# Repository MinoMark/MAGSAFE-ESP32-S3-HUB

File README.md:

# MAGSAFE ESP32-S3 HUB
**Don't get up, just use this...**

(Read bottom before reading BOM)

## About My Project

What is my project? My project is one of a kind! I am using an ESP32-S3 microcontroller chip to power a smart 2.8" TFT touchscreen. As mentioned in the title, it is listed as being MagSafe compatible, which is ingenious, right? Who does not want to have it charging 24/7? Or maybe not? Well, that has been solved too! I have added a 3.7V 5000mAh LiPo battery that can last well over 24 hours. But that is not all! I have also included an audio amplifier with a super loud and crisp speaker so you can hear those alerts and alarms from meters away.

I’ve made this project because I am tired of opening my laptop just to have a look at the time, set a timer, turn on smart lights, or do almost anything else. With my design, I’ll be able to control these all in one. You can have it play soothing music or play annoying alarms whenever.

**How to use:**

Plug it into the dedicated USB-C port at the bottom side with a USB-C cable or any compatible iPhone MagSafe charger. Let it charge for 10 minutes to an hour to fully charge. For MagSafe, let it charge for 30 minutes to an hour and 15 minutes.

## Schematics
The schematics of my final design, what I'll be using to make the main PCB.

## PCB
The fully routed PCB, with fun easter egg and smart eletrical wiring choices that save money and change the path of electricity more efficiently.

## CAD
A full design of the parts (except some models impossible to source)
.png>) 
.png>) 
.png>)

## BOM

| Part | Type | Quantity | Unit price (AUD) | Line total (AUD) | Link | Vendor | Funding | Notes | Index | LCSC# | MPN | Package | RoHS | MOQ | Multiple |
|---|---|---:|---:|---:|---|---|---|---|---:|---|---|---|---|---:|---:|
| 0Ω ±1% 62.5mW 0402 Thick Film Resistor | Part | 4 | 0.0011 | 0.0044 | https://www.lcsc.com/product-detail/C17168.html | UNI-ROYAL | Grant | This is min you can buy | 1 | C17168 | 0402WGF0000TCE | 0402 | yes | 100 | 100 |
| Crystal 32.768kHz ±20ppm 6pF 55kΩ SMD3215-2P | Part | 2 | 0.6046 | 0.60 | https://www.lcsc.com/product-detail/C1985240.html | ABRACON | Grant | This is min you can buy | 2 | C1985240 | ABS07-120-32.768KHZ-T | SMD3215-2P | yes | 1 | 1 |
| 3.3V Positive Fixed SOT-89-5 Voltage Regulators - Linear, Low Drop Out (LDO) Regulators RoHS | Part | 2 | 0.5913 | 0.59 | https://www.lcsc.com/product-detail/C460397.html | DIODES | Grant | This is min you can buy | 3 | C460397 | AP7361C-33Y5-13 | SOT-89-5 | yes | 1 | 1 |
| 14VC Clamp 5.5A Ipp ESD DIODE SOT-666-6 | Part | 2 | 0.1571 | 0.79 | https://www.lcsc.com/product-detail/C2827693.html | TECH PUBLIC | Grant | This is min you can buy | 4 | C2827693 | USBLC6-2P6 | SOT-666-6 | yes | 5 | 5 |
| Tactile Switch SPST 250gf 2.5mm Gull Wing 6.1mm x 3.7mm Surface Mount | Part | 4 | 0.0415 | 0.42 | https://www.lcsc.com/product-detail/C255802.html | HYP | Grant | This is min you can buy | 5 | C255802 | 1TS002E-2500-2501-CT | SMD,6x3.7mm | yes | 10 | 10 |
| 22Ω ±1% 62.5mW 0402 Thick Film Resistor | Part | 4 | 0.0019 | 0.0076 | https://www.lcsc.com/product-detail/C25092.html | UNI-ROYAL | Grant | This is min you can buy | 6 | C25092 | 0402WGF220JTCE | 0402 | yes | 100 | 100 |
| 5.1kΩ ±1% 62.5mW 0402 Thick Film Resistor | Part | 4 | 0.0023 | 0.0092 | https://www.lcsc.com/product-detail/C25905.html | UNI-ROYAL | Grant | This is min you can buy | 7 | C25905 | 0402WGF5101TCE | 0402 | yes | 100 | 100 |
| 100nF ±10% 50V Ceramic Capacitor X7R 0402 | Part | 2 | 0.009 | 0.018 | https://www.lcsc.com/product-detail/C307331.html | Samsung Electro-Mechanics | Grant | This is min you can buy | 8 | C307331 | CL05B104KB54PNC | 0402 | yes | 100 | 100 |
| Pre-Biased Bipolar Transistor (BJT) 50V 100mA 150mW Surface Mount SOT-363 | Part | 2 | 0.0502 | 0.50 | https://www.lcsc.com/product-detail/C62892.html | JSCJ | Grant | This is min you can buy | 9 | C62892 | UMH3N | SOT-363 | yes | 10 | 10 |
| 22Ω ±5% 62.5mW 0402 Thick Film Resistor | Part | 4 | 0.0017 | 0.0068 | https://www.lcsc.com/product-detail/C25152.html | UNI-ROYAL | Grant | This is min you can buy | 10 | C25152 | 0402WGJ0220TCE | 0402 | yes | 100 | 100 |
| DIODES AP2112K-3.3TRG1 | Part | 4 | 0.1848 | 0.7392 | https://www.lcsc.com/product-detail/C51118.html?s_z=n_q_c51118&globalKeyword=c51118 | DIODES | Grant | This is min you can buy | 11 | C51118 | AP2112K-3.3TRG1 | SOT-25-5 | yes | 5 | 5 |
| 2.4GHz ESP32-S3R8 -103.5dBm SMD,19.2x18mm RF Transceiver Modules and Modems RoHS | Part | 2 | 5.2355 | 5.24 | https://www.lcsc.com/product-detail/C3013946.html | ESPRESSIF | Grant | This is min you can buy | 12 | C3013946 | ESP32-S3-WROOM-1U-N16R8 | SMD,19.2x18mm | yes | 1 | 1 |
| USB-C (USB TYPE-C) Receptacle Connector 16 Position Surface Mount | Part | 2 | 0.1736 | 0.87 | https://www.lcsc.com/product-detail/C165948.html | Korean Hroparts Elec | Grant | This is min you can buy | 13 | C165948 | TYPE-C-31-M-12 | SMD | yes | 5 | 5 |
| 14.1VC Clamp 11.2A Ipp TVS DIODE SOD-523 | Part | 2 | 0.0487 | 0.49 | https://www.lcsc.com/product-detail/C61148.html | onsemi | Grant | This is min you can buy | 14 | C61148 | ESD5Z3.3T1G | SOD-523 | yes | 10 | 10 |
| Red 625nm LED Indication - Discrete 2.3V 0603 | Part | 2 | 0.0036 | 0.0072 | https://www.lcsc.com/product-detail/C965799.html | XINGLIGHT | Grant | This is min you can buy | 15 | C965799 | XL-1608SURC-06 | 0603 | yes | 100 | 100 |
| Diode Independent 40V 3A Surface Mount SMA(DO-214AC) | Part | 6 | 0.0337 | 0.67 | https://www.lcsc.com/product-detail/C8678.html | MDD(Microdiode Semiconductor) | Grant | This is min you can buy | 16 | C8678 | SS34 | SMA(DO-214AC) | yes | 20 | 20 |
| 22uF ±20% 25V Ceramic Capacitor X5R 0805 | Part | 2 | 0.1852 | 3.70 | https://www.lcsc.com/product-detail/C45783.html | Samsung Electro-Mechanics | Grant | This is min you can buy | 17 | C45783 | CL21A226MAQNNNE | 0805 | yes | 20 | 20 |
| 10uF ±20% 10V Ceramic Capacitor X5R 0402 | Part | 10 | 0.0304 | 1.82 | https://www.lcsc.com/product-detail/C315248.html | Samsung Electro-Mechanics | Grant | This is min you can buy | 18 | C315248 | CL05A106MP5NUNC | 0402 | yes | 20 | 20 |
| 1uF ±10% 25V Ceramic Capacitor X5R 0402 | Part | 2 | 0.0059 | 0.0118 | https://www.lcsc.com/product-detail/C52923.html | Samsung Electro-Mechanics | Grant | This is min you can buy | 19 | C52923 | CL05A105KA5NQNC | 0402 | yes | 100 | 100 |
| MAX98357A audio amplifier | Part | 1 | 3.01 | 3.01 | https://www.aliexpress.com/item/1005007003802663.html?spm=a2g0o.productlist.main.4.2bd23ce0doG6x8&aem_p4p_detail=202611050133081315319932123740002772996&algo_pvid=0ad6be40-46e3-4f00-9430-e9820924795f&algo_exp_id=0ad6be40-46e3-4f00-9430-e9820924795f-3&pdp_ext_f=%7B%22order%22%3A%223834%22%2C%22spu_best_type%22%3A%22price%22%2C%22eval%22%3A%221%22%2C%22fromPage%22%3A%22search%22%7D&pdp_npi=6%40dis%21AUD%212.99%212.84%21%21%2113.80%2113.11%21%402101ca9517938711880116699e0d41%2112000052658790894%21sea%21AU%212961347876%21X%211%210%21n_tag%3A-29919%3Bd%3A20f6a0d2%3Bm03_new_user%3A-29895%3BpisId%3A5000000220905999&curPageLogUid=gHNWoxg3Cup0&utparam-url=scene%3Asearch%7Cquery_from%3A%7Cx_object_id%3A1005007003802663%7C_p_origin_prod%3A&search_p4p_id=202611050133081315319932123740002772996_1 | AliExpress | Grant | | 20 | N/A | N/A | 1PCS | yes | 1 | 1 |
| Wireless charger receiver | Part | 1 | 4.26 | 4.26 | https://www.aliexpress.com/item/1005006917890401.html?spm=a2g0o.productlist.main.21.5befc5e30wHdxF&algo_pvid=c3f727d4-7764-4de2-9cfe-4073aea75173&algo_exp_id=c3f727d4-7764-4de2-9cfe-4073aea75173-18&pdp_ext_f=%7B%22order%22%3A%22260%22%2C%22spu_best_type%22%3A%22price%22%2C%22eval%22%3A%22price%22%2C%22fromPage%22%3A%22search%22%7D&pdp_npi=6%40dis%21AUD%213.98%213.49%21%21%212.75%212.41%21%402101d2e717938715347906588e0f1b%2112000038722150536%21sea%21AU%212961347876%21X%211%210%21n_tag%3A-29919%3Bd%3A20f6a0d2%3Bm03_new_user%3A-29895%3BpisId%3A5000000220770329&curPageLogUid=ptJgFovmIGzU&utparam-url=scene%3Asearch%7Cquery_from%3A%7Cx_object_id%3A1005006917890401%7C_p_origin_prod%3A | AliExpress | Grant | | 21 | N/A | N/A | 5W | yes | 1 | 1 |
| Battery management board | Part | 1 | 1.06 | 1.06 | https://www.aliexpress.com/item/1005013472412754.html?spm=a2g0o.productlist.main.9.7fb4e999hY7Rre&algo_pvid=98fe2f10-0cd6-416a-bbd2-9b577de21ebe&algo_exp_id=98fe2f10-0cd6-416a-bbd2-9b577de21ebe-8&pdp_ext_f=%7B%22order%22%3A%225%22%2C%22spu_best_type%22%3A%22price%22%2C%22eval%22%3A%221%22%2C%22fromPage%22%3A%22search%22%7D&pdp_npi=6%40dis%21AUD%212.45%210.97%21%21%2111.31%214.51%21%402101d33417938729376868658e0dc7%2112000061234386246%21sea%21AU%212961347876%21X%211%210%21n_tag%3A-29919%3Bd%3A20f6a0d2%3Bm03_new_user%3A-29895%3BpisId%3A5000000220868114&curPageLogUid=SZ1nXcZwQJOj&utparam-url=scene%3Asearch%7Cquery_from%3A%7Cx_object_id%3A1005013472412754%7C_p_origin_prod%3A | AliExpress | Grant | | 22 | N/A | N/A | 1X-Type C | yes | 1 | 1 |
| 955565 3.7V 5000mAh Polymer Lithium Battery | Part | 1 | 12.47 | 12.47 | https://www.aliexpress.com/item/1005013156740117.html?spm=a2g0o.productlist.main.2.398348ee8Gn6zi&algo_pvid=f6f2868e-1781-4497-a01c-ee345d06bc3b&algo_exp_id=f6f2868e-1781-4497-a01c-ee345d06bc3b-1&pdp_ext_f=%7B%22order%22%3A%222%22%2C%22spu_best_type%22%3A%22price%22%2C%22eval%22%3A%22price%22%2C%22fromPage%22%3A%22search%22%7D&pdp_npi=6%40dis%21AUD%2120.14%2112.69%21%21%2192.85%2158.50%21%4021030f8317938734351546746e0d36%2112000060361345573%21sea%21AU%212961347876%21X%211%210%21n_tag%3A-29919%3Bd%3A20f6a0d2%3Bm03_new_user%3A-29895 | AliExpress | Grant | | 23 | N/A | N/A | 955565 1PCS | yes | 1 | 1 |
| Speaker | Part | 1 | 2.54 | 2.54 | https://www.aliexpress.com/item/1005007640238935.html?spm=a2g0o.detail.pcDetailTopMoreOtherSeller.4.6cacshuCshuCnA&gps-id=pcDetailTopMoreOtherSeller&scm=1007.40050.354490.0&scm_id=1007.40050.354490.0&scm-url=1007.40050.354490.0&pvid=b61e8163-83fe-4c95-9dc5-7b9f26661546&_t=gps-id%3ApcDetailTopMoreOtherSeller%2Cscm-url%3A1007.40050.354490.0%2Cpvid%3Ab61e8163-83fe-4c95-9dc5-7b9f26661546%2Ctpp_buckets%3A668%232846%238110%231995&pdp_ext_f=%7B%22order%22%3A%222631%22%2C%22eval%22%3A%221%22%2C%22sceneId%22%3A%2230050%22%2C%22fromPage%22%3A%22recommend%22%7D&pdp_npi=6%40dis%21AUD%214.06%213.69%21%21%2118.49%2116.82%21%402103117b17940474651706506e0d0b%2112000041608234950%21rec%21AU%212961347876%21XZ%211%210%21n_tag%3A-29919%3Bd%3A20f6a0d2%3Bm03_new_user%3A-29895%3BpisId%3A5000000220905999&utparam-url=scene%3ApcDetailTopMoreOtherSeller%7Cquery_from%3A%7Cx_object_id%3A1005007640238935%7C_p_origin_prod%3A | AliExpress | Grant | | 24 | N/A | N/A | 2535 4 ohm 3W | yes | 1 | 1 |
| 2.8" Touch LCD Screen | Part | 1 | 7.67 | 7.67 | https://www.aliexpress.com/item/1005008556130457.html?spm=a2g0o.detail.pcDetailTopMoreOtherSeller.12.6cacshuCshuCnA&gps-id=pcDetailTopMoreOtherSeller&scm=1007.40050.354490.0&scm_id=1007.40050.354490.0&scm-url=1007.40050.354490.0&pvid=b61e8163-83fe-4c95-9dc5-7b9f26661546&_t=gps-id%3ApcDetailTopMoreOtherSeller%2Cscm-url%3A1007.40050.354490.0%2Cpvid%3Ab61e8163-83fe-4c95-9dc5-7b9f26661546%2Ctpp_buckets%3A668%232846%238110%231995&pdp_ext_f=%7B%22order%22%3A%222115%22%2C%22spu_best_type%22%3A%22price%22%2C%22eval%22%3A%221%22%2C%22sceneId%22%3A%2230050%22%2C%22fromPage%22%3A%22recommend%22%7D&pdp_npi=6%40dis%21AUD%2135.60%2131.55%21%21%21162.02%21143.60%21%402103117b17940474651706506e0d0b%2112000045695652679%21rec%21AU%212961347876%21XZ%211%210%21n_tag%3A-29919%3Bd%3A20f6a0d2%3Bm03_new_user%3A-29895%3BpisId%3A5000000221234826&utparam-url=scene%3ApcDetailTopMoreOtherSeller%7Cquery_from%3A%7Cx_object_id%3A1005008556130457%7C_p_origin_prod%3A | AliExpress | Already own | | 25 | N/A | N/A | 2.8 Inch LCD | yes | 1 | 1 |
| AliExpress Shipping (Australia) | Shipping | 1 | 3.02 | 3.02 | https://www.aliexpress.com/?src=google&albch=fbrnd&acnt=347-178-5672&isdl=y&aff_short_key=UneMJZVf&albcp=22321354204&albag=178985906351&slnk=&trgt=kwd-14802285088&plac=&crea=737351379802&netw=g&device=c&mtctp=e&memo1=&albbt=Google_7_fbrnd&aff_platform=google&albagn=888888&isSmbActive=false&isSmbAutoCall=false&needSmbHouyi=false&gad_source=1&gad_campaignid=22321354204&gbraid=0AAAAAD1qHibUcQdrYeOuuBWuvApxTQOP2&gclid=CjwKCAiAtbvXBhB_EiwAjwv9Jjyvq29gqiMRapaex5iaRvapHnvC2KuxCO2ai3P2B7r6hRykpAxdUhoCgLwQAvD_BwE | AliExpress | Grant | | 26 | N/A | N/A | N/A | N/A | N/A | N/A |
| AliExpress tax | Tax or fee | 1 | 2.52 | 2.52 | https://www.aliexpress.com/?src=google&albch=fbrnd&acnt=347-178-5672&isdl=y&aff_short_key=UneMJZVf&albcp=22321354204&albag=178985906351&slnk=&trgt=kwd-14802285088&plac=&crea=737351379802&netw=g&device=c&mtctp=e&memo1=&albbt=Google_7_fbrnd&aff_platform=google&albagn=888888&isSmbActive=false&isSmbAutoCall=false&needSmbHouyi=false&gad_source=1&gad_campaignid=22321354204&gbraid=0AAAAAD1qHibUcQdrYeOuuBWuvApxTQOP2&gclid=CjwKCAiAtbvXBhB_EiwAjwv9Jjyvq29gqiMRapaex5iaRvapHnvC2KuxCO2ai3P2B7r6hRykpAxdUhoCgLwQAvD_BwE | AliExpress | Grant | | 27 | N/A | N/A | N/A | N/A | N/A | N/A |
| PCBA & PCBA | PCB | 1 | 149.00 | 149.00 | https://jlcpcb.com/?from=VGS&utm_source=google&utm_medium=cpc&utm_campaign=14177189905&gad_source=1&gad_campaignid=14177189905&gbraid=0AAAAABS1Qql1GOgRJWfW55GGh4BVLQ-kr&gclid=CjwKCAiA2MDXBhBUEiwAD-YB-_knJwTwOTv6-qw0cwhvcRU1fMAk8eRsxDyDG89k4pFLfxfHsxuqEBoCV9sQAvD_BwE | JLCONE | Grant | It says in the photo its $150 AUD, but im buying from us so its ok. | 28 | N/A | N/A | N/A | no | N/A | N/A |
| **Total** | | | | **202.0442** | | | | | | | | | | | |
| **Grant total** | | | | **194.3742** | | | | | | | | | | | |

# IMPORTANT READ BELOW

**Just to let you know:**

The total for the PCB is $150 AUD, plus $25 AUD for the AliExpress modules, bringing the actual total to $175 AUD.
You might notice the Bill of Materials (BOM) shows a total of around $200 AUD. This looks high because the BOM lists the individual prices of every single component. However, the PCB and PCBA prices already include the cost of these parts and their assembly.

I included the individual parts in the list just to show the breakdown, but you do not need to buy them separately. Since they are already covered in the PCBA price, they will not be added to the final cost.

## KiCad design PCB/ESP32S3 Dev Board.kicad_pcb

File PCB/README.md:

# All My Schematics and PCB Designs

**About My Design**

I have used many different things in my schematic I have never used before with some of these actually helping and others for convenience.

## What Happened

When making the schematic and testing to see if every part was in LCSC I found out that there was one 3V3 LDO chip that was out of stock. Because of this I had to remove a resistor remove that chip and replace it with my existing chip that you see now on the schematic.

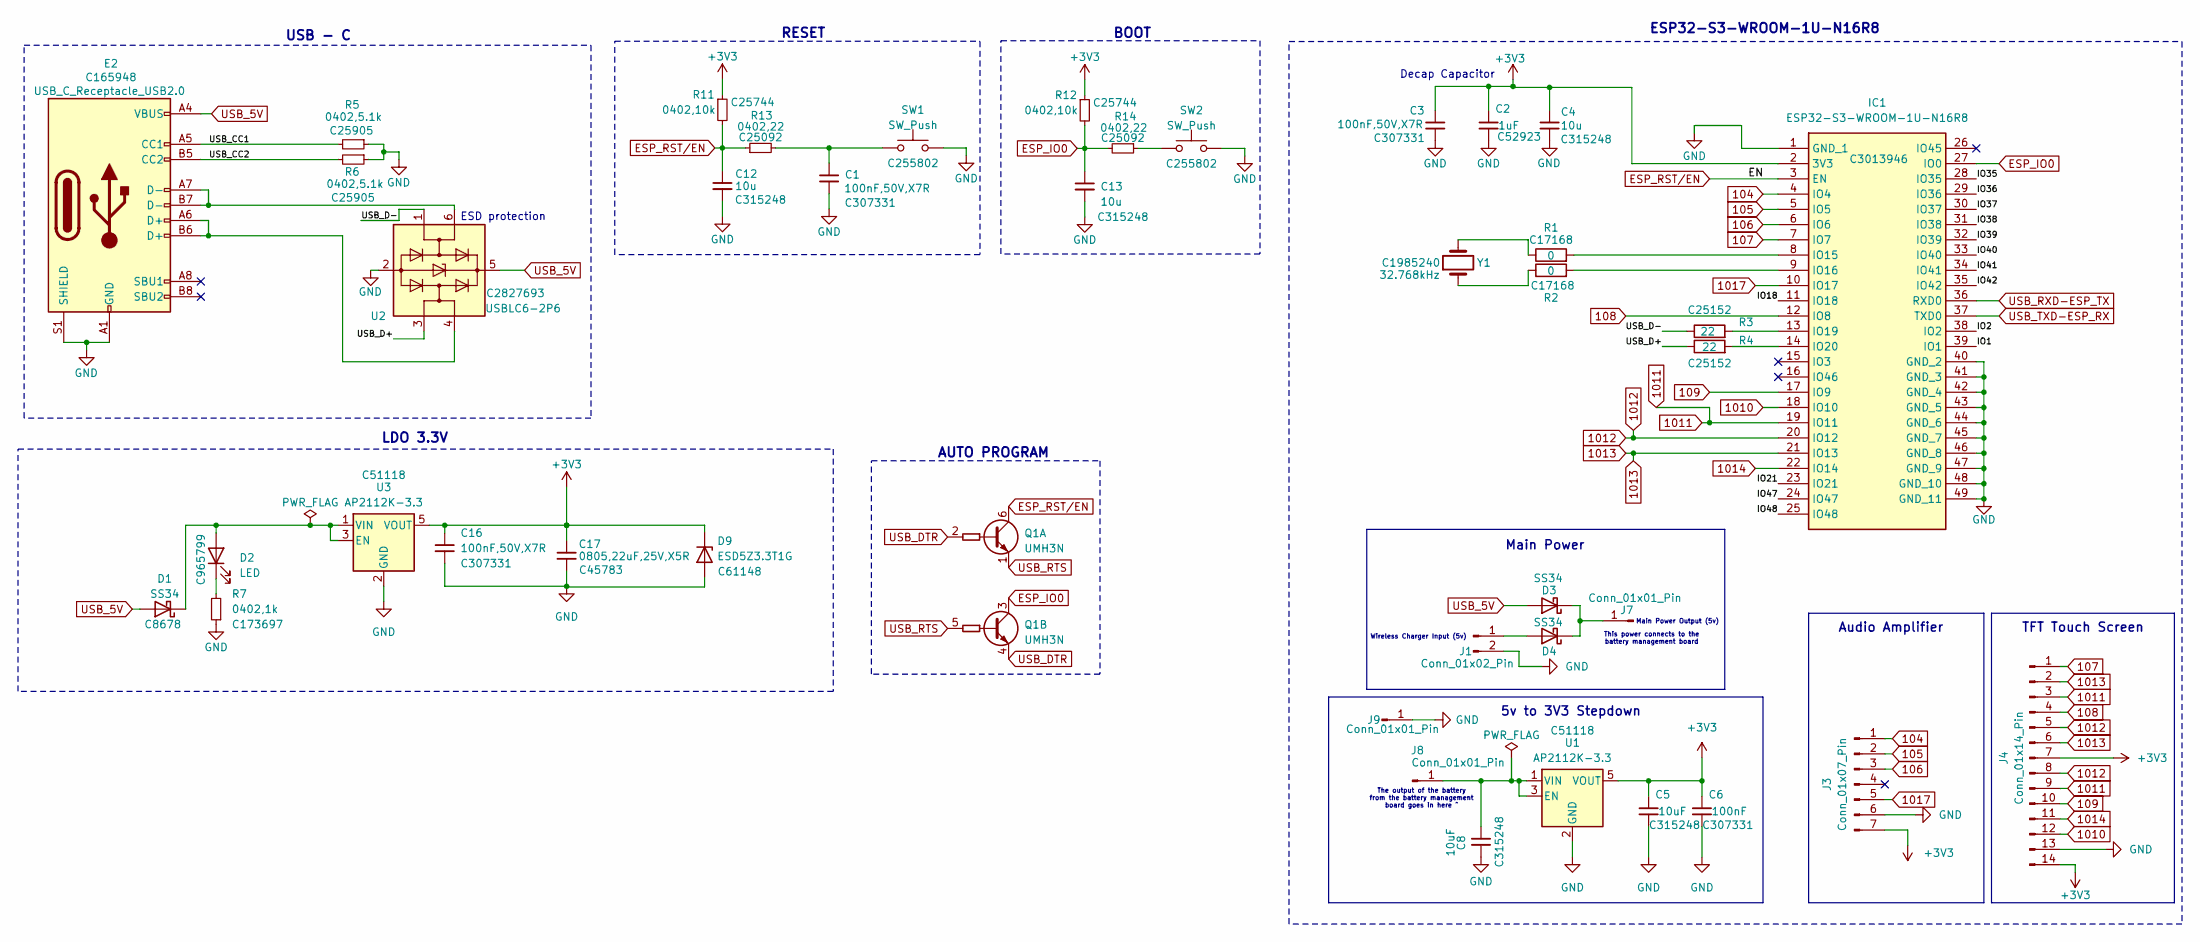
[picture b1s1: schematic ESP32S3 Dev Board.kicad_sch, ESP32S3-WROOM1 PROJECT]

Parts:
C1, C3, C16: 100nF,50V,X7R; C_0402_1005Metric; Manufacturer_Part_Number CL05B104KB54PNC; LCSC C307331
C2: 1uF; C_0402_1005Metric; Manufacturer_Part_Number CL05A105KA5NQNC; LCSC C52923
C4: 10u; C_0402_1005Metric; Manufacturer_Part_Number CL05B104KB54PNC; LCSC C315248
C5, C8: 10uF; C_0402_1005Metric; Manufacturer_Part_Number CL05A106MP5NUNC; LCSC C315248
C6: 100nF; C_0402_1005Metric; Manufacturer_Part_Number CL05B104KB54PNC; LCSC C307331
C12, C13: 10u; C_0402_1005Metric; Manufacturer_Part_Number CL05A106MP5NUNC; LCSC C315248
C17: 0805,22uF,25V,X5R; C_0805_2012Metric; Manufacturer_Part_Number CL21A226MAQNNNE; LCSC C45783
D1, D3, D4: SS34; D_SMA; Manufacturer_Part_Number SS34; LCSC C8678
D2: LED; LED_0603_1608Metric; MPN XL-1608SURC-06; LCSC C965799
D9: ESD5Z3.3T1G; D_SOD-523; Manufacturer_Part_Number ESD5Z3.3T1G; LCSC C61148
E2: USB_C_Receptacle_USB2.0; USB_C_Receptacle_HRO_TYPE-C-31-M-12; Manufacturer_Part_Number TYPE-C-31-M-12; LCSC C165948
IC1: ESP32-S3-WROOM-1U-N16R8; ESP32-S3-WROOM-1U; Mouser Part Number 356-ESP32S3WM1UN16R8
J1: Conn_01x02_Pin; PinHeader_1x02_P2.54mm_Vertical; LCSC N/A
J3: Conn_01x07_Pin; PinHeader_1x07_P2.54mm_Vertical; LCSC N/A
J4: Conn_01x14_Pin; PinHeader_1x14_P2.54mm_Vertical; LCSC N/A
J7, J8, J9: Conn_01x01_Pin; SolderWirePad_1x01_SMD_1.5x3mm; LCSC N/A
Q1: UMH3N; SOT-363_SC-70-6; Manufacturer_Part_Number UMH3N; LCSC C62892
R1, R2: 0; C_0402_1005Metric; Manufacturer_Part_Number 0402WGF0000TCE; LCSC C17168
R3, R4: 22; C_0402_1005Metric; Manufacturer_Part_Number 0402WGJ0220TCE; LCSC C25152
R5, R6: 0402,5.1k; R_0402_1005Metric; Manufacturer_Part_Number 0402WGF5101TCE; LCSC C25905
R7: 0402,1k; R_0402_1005Metric; Manufacturer_Part_Number 0402WGF1002TCE; LCSC C173697
R11, R12: 0402,10k; R_0402_1005Metric; Manufacturer_Part_Number 0402WGF1002TCE; LCSC C25744
R13, R14: 0402,22; R_0402_1005Metric; Manufacturer_Part_Number 0402WGF220JTCE; LCSC C25092
SW1, SW2: SW_Push; SW_SPST_CK_RS282G05A3; Manufacturer_Part_Number 1TS002E-2500-2501-CT; LCSC C255802
U1, U3: AP2112K-3.3; SOT-23-5; Manufacturer_Part_Number AP2112K-3.3TRG1; LCSC C51118
U2: USBLC6-2P6; SOT-666; Manufacturer_Part_Number USBLC6-2P6; LCSC C2827693
Y1: 32.768kHz; Crystal_SMD_3215-2Pin_3.2x1.5mm; Manufacturer_Part_Number ABS07-120-32.768KHZ-T; LCSC C1985240

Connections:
104: IC1.4 (IO4), J3.1
105: IC1.5 (IO5), J3.2
106: IC1.6 (IO6), J3.3
107: IC1.7 (IO7), J4.1
108: IC1.12 (IO8), J4.4
109: IC1.17 (IO9), J4.10
1010: IC1.18 (IO10), J4.12
1011: IC1.19 (IO11), J4.3, J4.9
1012: IC1.20 (IO12), J4.5, J4.8
1013: IC1.21 (IO13), J4.2, J4.6
1014: IC1.22 (IO14), J4.11
1017: IC1.10 (IO17), J3.5
+3V3: C2.1, C3.1, C4.1, C5.1, C6.1, C16.1, C17.1, D9.1 (K), IC1.2 (3V3), J3.7, J4.7, J4.14, R11.1, R12.1, U1.5 (VOUT), U3.5 (VOUT)
/IO1: IC1.39 (IO1)
/IO2: IC1.38 (IO2)
/IO18: IC1.11 (IO18)
/IO21: IC1.23 (IO21)
/IO35: IC1.28 (IO35)
/IO36: IC1.29 (IO36)
/IO37: IC1.30 (IO37)
/IO38: IC1.31 (IO38)
/IO39: IC1.32 (IO39)
/IO40: IC1.33 (IO40)
/IO41: IC1.34 (IO41)
/IO42: IC1.35 (IO42)
/IO47: IC1.24 (IO47)
/IO48: IC1.25 (IO48)
/USB_CC1: E2.A5 (CC1), R5.2
/USB_CC2: E2.B5 (CC2), R6.2
/USB_D+: R4.1, U2.3 (I/O2)
/USB_D-: R3.1, U2.1 (I/O1)
ESP_IO0: C13.1, IC1.27 (IO0), Q1.3 (C2), R12.2, R14.2
ESP_RST/EN: C12.1, IC1.3 (EN), Q1.6 (C1), R11.2, R13.1
GND: C1.2, C2.2, C3.2, C4.2, C5.2, C6.2, C8.1, C12.2, C13.2, C16.2, C17.2, D9.2 (A), E2.A1 (GND), E2.A12 (GND), E2.B1 (GND), E2.B12 (GND), E2.S1 (SHIELD), IC1.1 (GND_1), IC1.40 (GND_2), IC1.41 (GND_3), IC1.42 (GND_4), IC1.43 (GND_5), IC1.44 (GND_6), IC1.45 (GND_7), IC1.46 (GND_8), IC1.47 (GND_9), IC1.48 (GND_10), IC1.49 (GND_11), J1.2, J3.6, J4.13, J9.1 (Pin_1_1), R5.1, R6.1, R7.1, SW1.2, SW2.2, U1.2 (GND), U2.2 (GND), U3.2 (GND)
unnamed: C1.1, R13.2, SW1.1
unnamed: D1.1 (K), D2.2 (A), U3.1 (VIN), U3.3 (EN)
unnamed: D2.1 (K), R7.2
unnamed: D3.1 (K), D4.1 (K), J7.1 (Pin_1_1)
unnamed: D4.2 (A), J1.1
unnamed: E2.A6 (D+), E2.B6 (D+), U2.4 (I/O2)
unnamed: E2.A7 (D-), E2.B7 (D-), U2.6 (I/O1)
unnamed: IC1.8 (IO15), R1.2
unnamed: IC1.9 (IO16), R2.2
unnamed: IC1.13 (IO19), R3.2
unnamed: IC1.14 (IO20), R4.2
unnamed: C8.2, J8.1 (Pin_1_1), U1.1 (VIN), U1.3 (EN)
unnamed: R1.1, Y1.2
unnamed: R2.1, Y1.1
unnamed: R14.1, SW2.1
USB_5V: D1.2 (A), D3.2 (A), E2.A4 (VBUS), E2.A9 (VBUS), E2.B4 (VBUS), E2.B9 (VBUS), U2.5 (VBUS)
USB_DTR: Q1.2 (B1), Q1.4 (E2)
USB_RTS: Q1.1 (E1), Q1.5 (B2)
USB_RXD-ESP_TX: IC1.36 (RXD0)
USB_TXD-ESP_RX: IC1.37 (TXD0)

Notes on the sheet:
TFT Touch Screen
BOOT
Decap Capacitor
LDO 3.3V
The output of the battery from the battery management board goes in here ^
USB - C
ESD protection
RESET
5v to 3V3 Stepdown
Main Power Output (5v)
Main Power
This power connects to the battery management board
Audio Amplifier
Wireless Charger Input (5v)
ESP32-S3-WROOM-1U-N16R8
AUTO PROGRAM

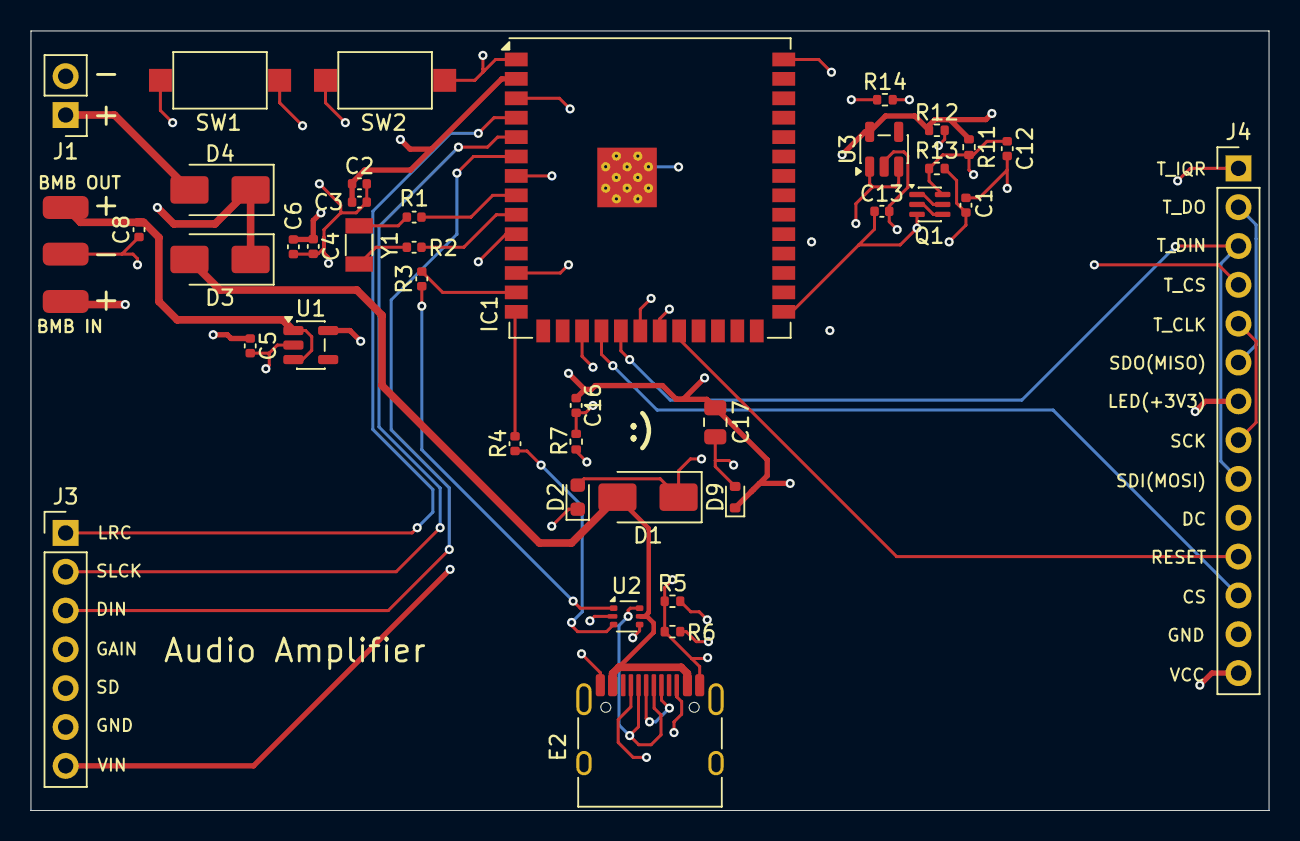
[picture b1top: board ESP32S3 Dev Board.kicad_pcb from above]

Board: 4 copper layers, 81.0 x 51.0 mm, 42 parts (0 on the bottom side), 38 nets.
